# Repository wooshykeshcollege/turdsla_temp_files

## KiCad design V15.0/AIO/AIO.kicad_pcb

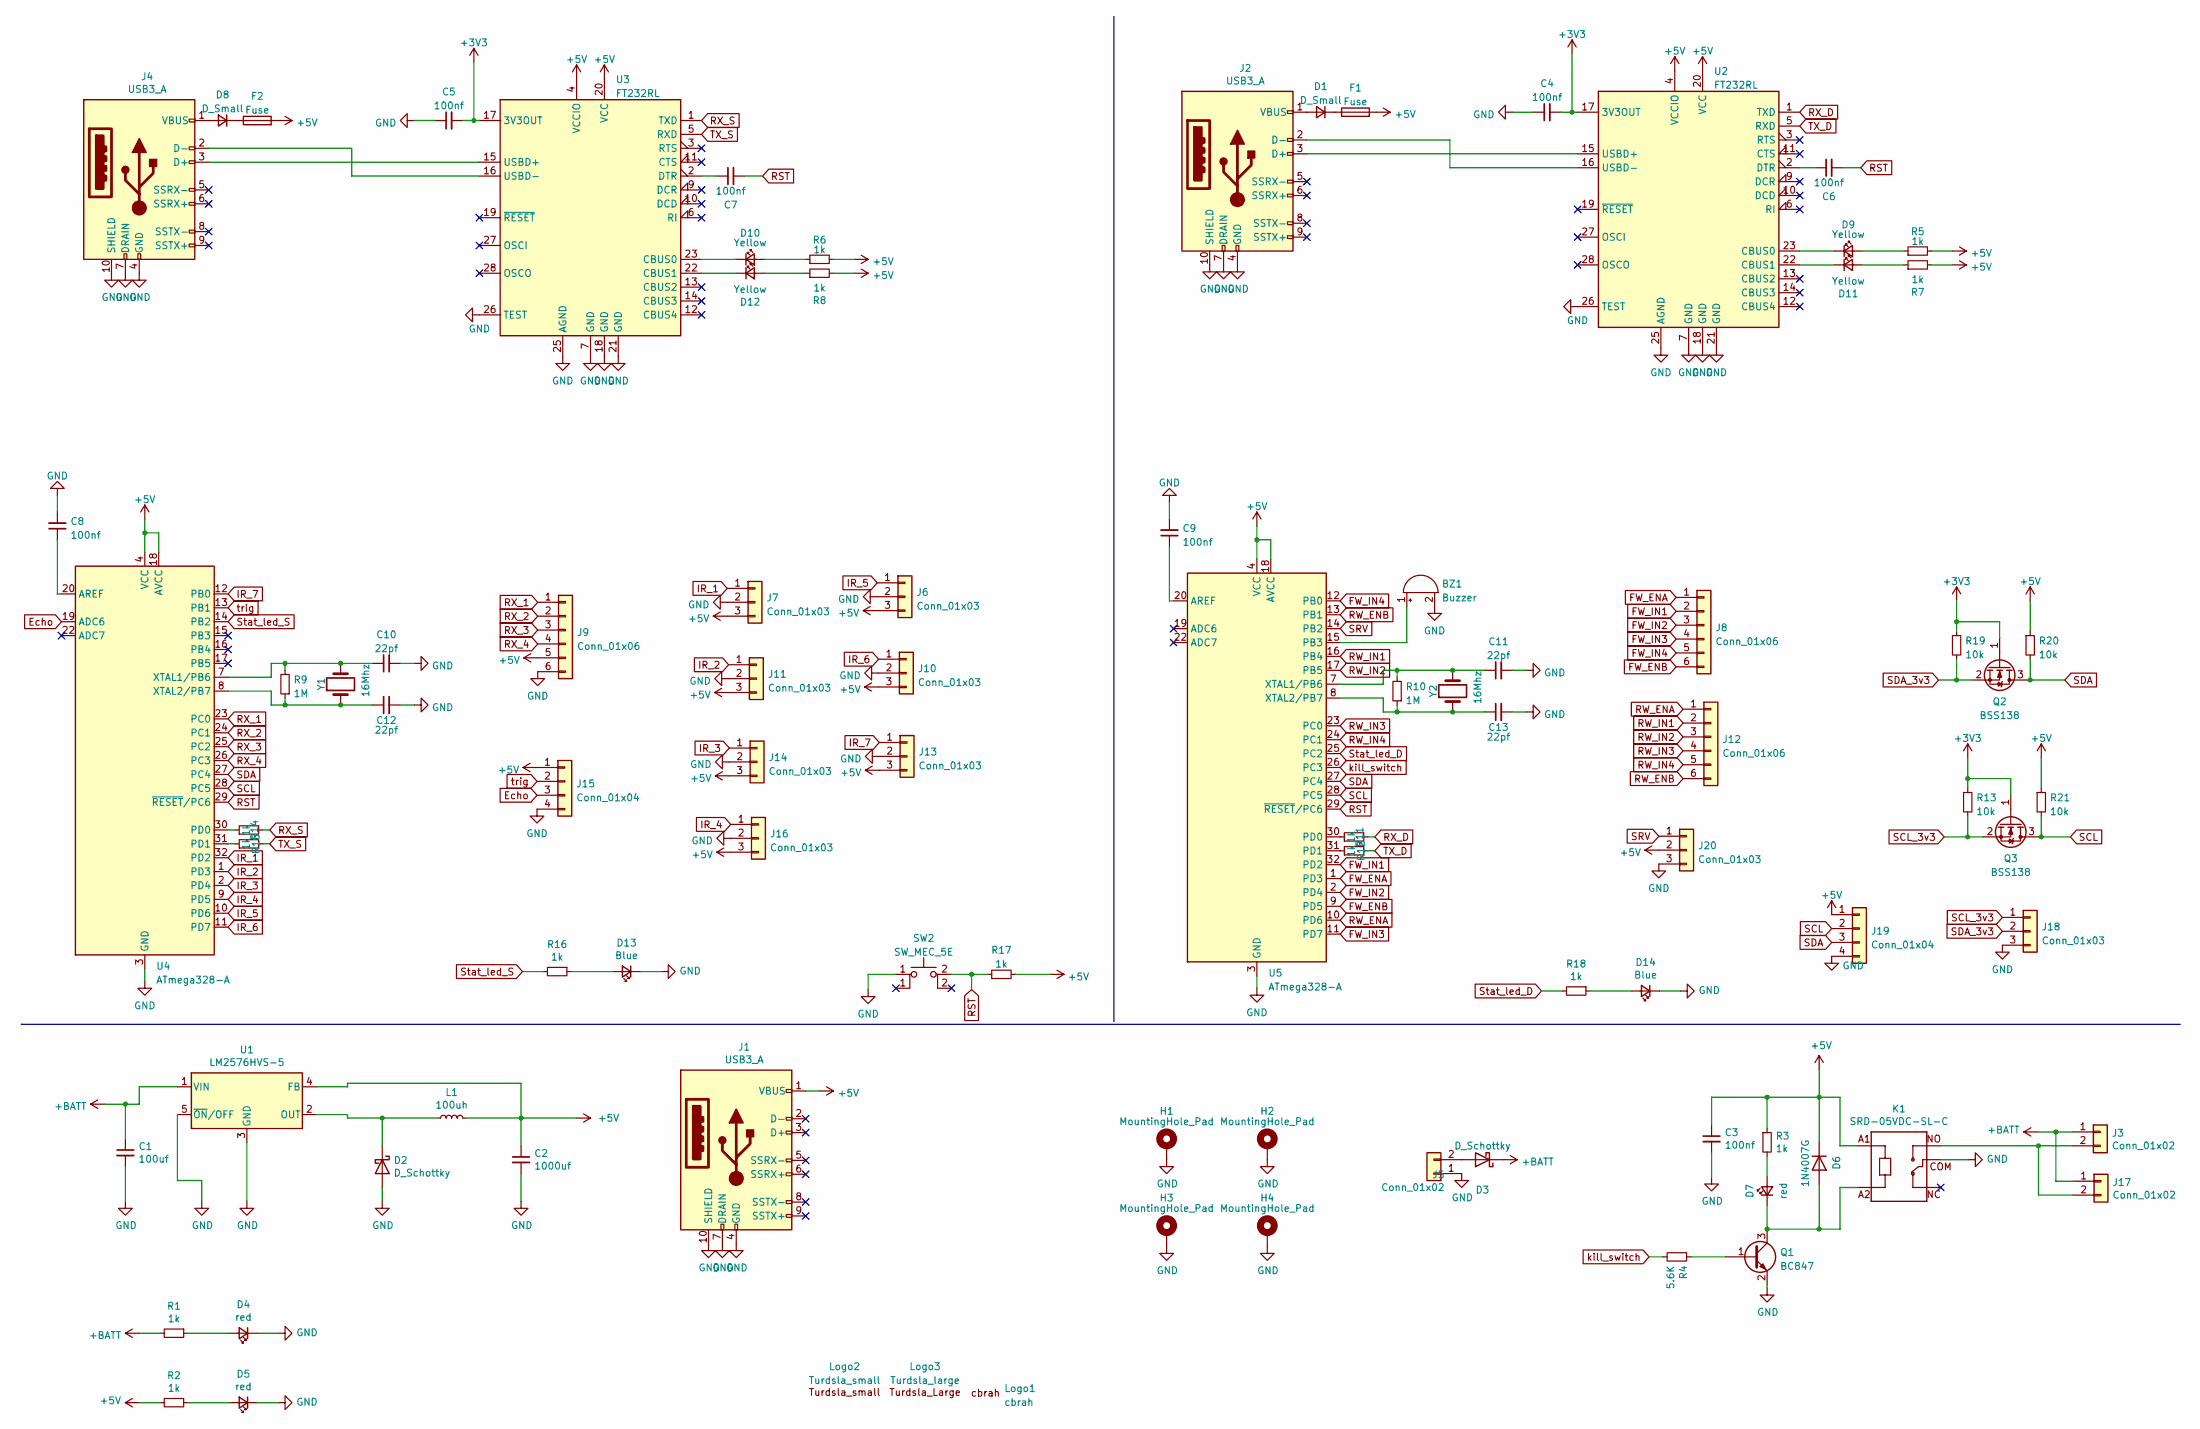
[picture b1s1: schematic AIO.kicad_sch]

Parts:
BZ1: Buzzer; MagneticBuzzer_ProSignal_ABI-009-RC
C1: 100uf; CP_Elec_6.3x7.7; LCSC PART# C72477
C2: 1000uf; cap_12.5x13.5; LCSC PART# C191226
C3, C4, C5, C6, C7, C8, C9: 100nf; C_1206_3216Metric; LCSC PART# C271438
C10, C11, C12, C13: 22pf; C_1206_3216Metric
D1, D8: D_Small; D_SOD-123
D2, D3: D_Schottky; schottky_diode; LCSC PART# C466483
D4, D5, D7: red; LED_1206_3216Metric; LCSC PART# C88326
D6: 1N4007G; SMAF; LCSC PART# C110856
D9, D10, D11, D12: Yellow; LED_1206_3216Metric; LCSC PART# C88326
D13, D14: Blue; LED_1206_3216Metric; LCSC PART# C88326
F1, F2: Fuse; Fuse_1210_3225Metric
H1, H2, H3, H4: MountingHole_Pad; MountingHole_3.2mm_M3_Pad_Via
J1, J2, J4: USB3_A; usb_3_female
J3, J17: Conn_01x02; TerminalBlock_bornier-2_P5.08mm
J5: Conn_01x02; AMASS_XT60-M_1x02_P7.20mm_Vertical
J6, J7, J10, J11, J13, J14, J16, J18, J20: Conn_01x03; PinHeader_1x03_P2.54mm_Vertical
J8, J9, J12: Conn_01x06; PinHeader_1x06_P2.54mm_Vertical
J15, J19: Conn_01x04; PinHeader_1x04_P2.54mm_Vertical
K1: SRD-05VDC-SL-C; Relay_SPDT_SANYOU_SRD_Series_Form_C; LCSC PART# C35449
L1: 100uh; LCSC PART# C408533
Logo1: cbrah; cbrah60
Logo2: Turdsla_small; Turdsla
Logo3: Turdsla_large
Q1: BC847; SOT-23
Q2, Q3: BSS138; SOT-23
R1, R2, R3, R5, R6, R7, R8, R11, R12, R14, R15, R16, R17, R18: 1k; R_1206_3216Metric; LCSC PART# C280032
R4: 5.6K; R_1206_3216Metric; LCSC PART# C844437
R9, R10: 1M; R_1206_3216Metric
R13, R19, R20, R21: 10k; R_1206_3216Metric; LCSC PART# C280032
SW2: SW_MEC_5E; SW_PUSH_6mm_H4.3mm
U1: LM2576HVS-5; TO-263-5_TabPin3; LCSC PART# C194472
U2, U3: FT232RL; SSOP-28_5.3x10.2mm_P0.65mm
U4, U5: ATmega328-A; TQFP-32_7x7mm_P0.8mm
Y1, Y2: 16Mhz; Crystal_SMD_SeikoEpson_MC405-2Pin_9.6x4.1mm

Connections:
+3V3: C4.2, C5.2, Q2.1 (G), Q3.1 (G), R13.1, R19.1, U2.17 (3V3OUT), U3.17 (3V3OUT)
+5V: C2.1, C3.1, D6.1 (K), F1.2, F2.2, J1.1 (VBUS), J6.3, J7.3, J9.5, J10.3, J11.3, J13.3, J14.3, J15.1, J16.3, J19.1, J20.2, K1.A1, L1.2, R2.2, R3.1, R5.2, R6.2, R7.2, R8.2, R17.2, R20.1, R21.1, U1.4 (FB), U2.4 (VCCIO), U2.20 (VCC), U3.4 (VCCIO), U3.20 (VCC), U4.4 (VCC), U4.6 (VCC), U4.18 (AVCC), U5.4 (VCC), U5.6 (VCC), U5.18 (AVCC)
+BATT: C1.1, D3.1 (K), J3.1, J17.1, R1.2, U1.1 (VIN)
Echo: J15.3, U4.19 (ADC6)
FW_ENA: J8.1, U5.1 (PD3)
FW_ENB: J8.6, U5.9 (PD5)
FW_IN1: J8.2, U5.32 (PD2)
FW_IN2: J8.3, U5.2 (PD4)
FW_IN3: J8.4, U5.11 (PD7)
FW_IN4: J8.5, U5.12 (PB0)
GND: BZ1.2 (+), C1.2, C2.2, C3.2, C4.1, C5.1, C8.2, C9.2, C10.2, C11.2, C12.2, C13.2, D2.2 (A), D4.1 (K), D5.1 (K), D13.1 (K), D14.1 (K), H1.1, H2.1, H3.1, H4.1, J1.4 (GND), J1.7 (DRAIN), J1.10 (SHIELD), J2.4 (GND), J2.7 (DRAIN), J2.10 (SHIELD), J4.4 (GND), J4.7 (DRAIN), J4.10 (SHIELD), J5.1, J6.2, J7.2, J9.6, J10.2, J11.2, J13.2, J14.2, J15.4, J16.2, J18.3, J19.4, J20.3, K1.COM, Q1.2 (E), SW2.1, U1.3 (GND), U1.5 (~ON/OFF), U2.7 (GND), U2.18 (GND), U2.21 (GND), U2.25 (AGND), U2.26 (TEST), U3.7 (GND), U3.18 (GND), U3.21 (GND), U3.25 (AGND), U3.26 (TEST), U4.3 (GND), U4.5 (GND), U4.21 (GND), U5.3 (GND), U5.5 (GND), U5.21 (GND)
IR_1: J7.1, U4.32 (PD2)
IR_2: J11.1, U4.1 (PD3)
IR_3: J14.1, U4.2 (PD4)
IR_4: J16.1, U4.9 (PD5)
IR_5: J6.1, U4.10 (PD6)
IR_6: J10.1, U4.11 (PD7)
IR_7: J13.1, U4.12 (PB0)
unnamed: BZ1.1 (-), U5.15 (PB3)
unnamed: C6.1, U2.2 (DTR)
unnamed: C7.1, U3.2 (DTR)
unnamed: C8.1, U4.20 (AREF)
unnamed: C9.1, U5.20 (AREF)
unnamed: C10.1, R9.2, U4.7 (XTAL1/PB6), Y1.2
unnamed: C11.1, R10.2, U5.7 (XTAL1/PB6), Y2.2
unnamed: C12.1, R9.1, U4.8 (XTAL2/PB7), Y1.1
unnamed: C13.1, R10.1, U5.8 (XTAL2/PB7), Y2.1
unnamed: D1.1 (K), F1.1
unnamed: D1.2 (A), J2.1 (VBUS)
unnamed: D2.1 (K), L1.1, U1.2 (OUT)
unnamed: D4.2 (A), R1.1
unnamed: D5.2 (A), R2.1
unnamed: D6.2 (A), D7.1 (K), K1.A2, Q1.3 (C)
unnamed: D7.2 (A), R3.2
unnamed: D8.1 (K), F2.1
unnamed: D8.2 (A), J4.1 (VBUS)
unnamed: D9.1 (K), U2.23 (CBUS0)
unnamed: D9.2 (A), R5.1
unnamed: D10.1 (K), U3.23 (CBUS0)
unnamed: D10.2 (A), R6.1
unnamed: D11.1 (K), U2.22 (CBUS1)
unnamed: D11.2 (A), R7.1
unnamed: D12.1 (K), U3.22 (CBUS1)
unnamed: D12.2 (A), R8.1
unnamed: D13.2 (A), R16.1
unnamed: D14.2 (A), R18.1
unnamed: J2.2 (D-), U2.16 (USBD-)
unnamed: J2.3 (D+), U2.15 (USBD+)
unnamed: J4.2 (D-), U3.16 (USBD-)
unnamed: J4.3 (D+), U3.15 (USBD+)
unnamed: D3.2 (A), J5.2
unnamed: J3.2, J17.2, K1.NO
unnamed: Q1.1 (B), R4.1
unnamed: R11.1, U5.30 (PD0)
unnamed: R12.1, U5.31 (PD1)
unnamed: R14.1, U4.30 (PD0)
unnamed: R15.1, U4.31 (PD1)
RST: C6.2, C7.2, R17.1, SW2.2, U4.29 (~RESET/PC6), U5.29 (~RESET/PC6)
RW_ENA: J12.1, U5.10 (PD6)
RW_ENB: J12.6, U5.13 (PB1)
RW_IN1: J12.2, U5.16 (PB4)
RW_IN2: J12.3, U5.17 (PB5)
RW_IN3: J12.4, U5.23 (PC0)
RW_IN4: J12.5, U5.24 (PC1)
RX_1: J9.1, U4.23 (PC0)
RX_2: J9.2, U4.24 (PC1)
RX_3: J9.3, U4.25 (PC2)
RX_4: J9.4, U4.26 (PC3)
RX_D: R11.2, U2.1 (TXD)
RX_S: R14.2, U3.1 (TXD)
SCL: J19.2, Q3.3 (D), R21.2, U4.28 (PC5), U5.28 (PC5)
SCL_3v3: J18.1, Q3.2 (S), R13.2
SDA: J19.3, Q2.3 (D), R20.2, U4.27 (PC4), U5.27 (PC4)
SDA_3v3: J18.2, Q2.2 (S), R19.2
SRV: J20.1, U5.14 (PB2)
Stat_led_D: R18.2, U5.25 (PC2)
Stat_led_S: R16.2, U4.14 (PB2)
TX_D: R12.2, U2.5 (RXD)
TX_S: R15.2, U3.5 (RXD)
kill_switch: R4.2, U5.26 (PC3)
trig: J15.2, U4.13 (PB1)

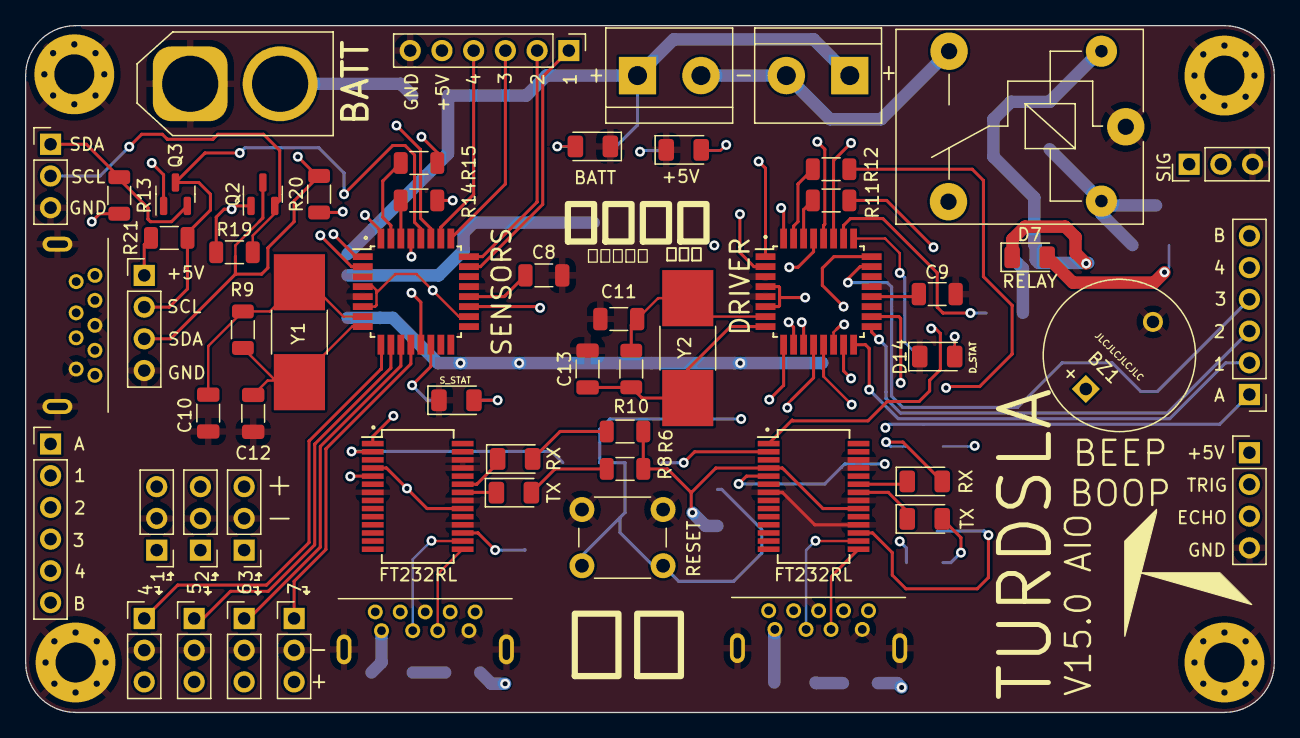
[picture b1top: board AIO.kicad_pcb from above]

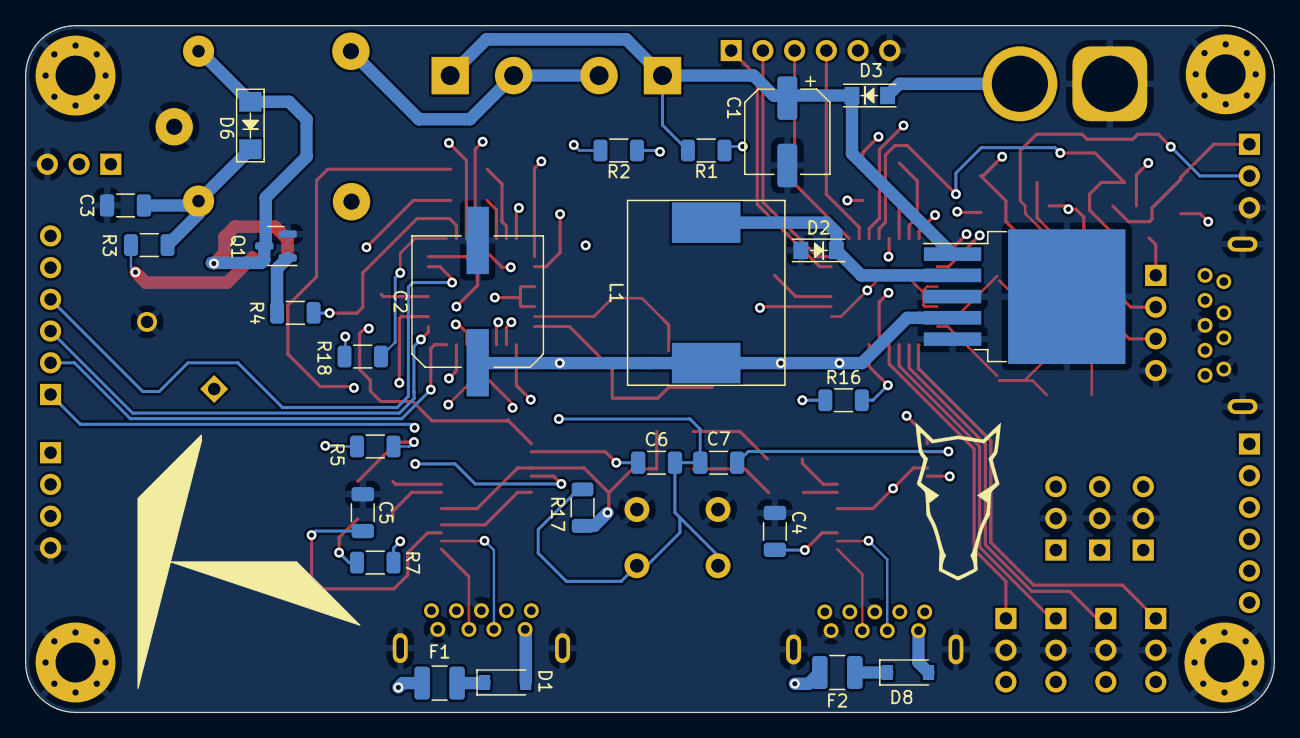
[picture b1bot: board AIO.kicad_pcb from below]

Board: 4 copper layers, 100.0 x 55.0 mm, 91 parts (28 on the bottom side), 81 nets.

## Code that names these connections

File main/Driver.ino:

#include <Wire.h>

int FW_IN1 = 2;
int FW_IN2 = 3;
int FW_IN3 = 4;
int FW_IN4 = 5;
int FW_ENA = A0;
int FW_ENB = A1;

int RW_IN1 = 6;
int RW_IN2 = 7;
int RW_IN3 = 8;
int RW_IN4 = 9;
int RW_ENA = A2;
int RW_ENB = A3;

int kill_Switch = 10;

int comm_led = 10;
int comm_count = 0;

int idrive[6] = {0};
string sdrive = "";
int check_flag = 0;

void setup()
{
    Serial.begin(38400);
    Wire.begin(0x8);
    Wire.onReceive(receive_Event);
    pinMode(FW_IN1, OUTPUT);
    pinMode(FW_IN2, OUTPUT);
    pinMode(FW_IN3, OUTPUT);
    pinMode(FW_IN4, OUTPUT);
    pinMode(RW_IN1, OUTPUT);
    pinMode(RW_IN2, OUTPUT);
    pinMode(RW_IN3, OUTPUT);
    pinMode(RW_IN4, OUTPUT);
    pinMode(FW_ENA, OUTPUT);
    pinMode(FW_ENB, OUTPUT);
    pinMode(RW_ENA, OUTPUT);
    pinMode(RW_ENB, OUTPUT);
    pinMode(kill_Switch, OUTPUT);
    digitalWrite(kill_Switch, HIGH);
}

void receive_Event()
{
    char c = Wire.read();
    switch (c)
    {
    case 2: // handshake
        Wire.write(1);
        break;
    case 3: // drive
        for (int i = 0; i < 6; i++)
        {
            drive[i] = wire.read();
            if(drive[i]==
        }

        break;
    case 4: // stop
        digitalWrite(FW_ENA, LOW);
        digitalWrite(FW_ENB, LOW);
        digitalWrite(RW_ENA, LOW);
        digitalWrite(RW_ENB, LOW);
        break;
    case 5: // kill
        digitalWrite(FW_ENA, LOW);
        digitalWrite(FW_ENB, LOW);
        digitalWrite(RW_ENA, LOW);
        digitalWrite(RW_ENB, LOW);
        digitalWrite(kill_Switch, LOW);
        break;

    case 5: // init
        digitalWrite(kill_Switch, HIGH);
        break;
    }
}
/// work with this first, run tests then use switch with one bit instruction input
void loop()
{
    ////
    if (comm_count % 30 == 0)
    {
        if (comm_status == 1)
        {
            digitalWrite(comm_led, LOW);
            comm_status = 0;
        }
        else if (comm_status == 0)
        {
            digitalWrite(comm_led, HIGH);
            comm_status = 1;
        }
    }
    comm_count++;
}
